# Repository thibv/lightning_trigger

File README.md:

# lightning_trigger
DSLR lightning trigger

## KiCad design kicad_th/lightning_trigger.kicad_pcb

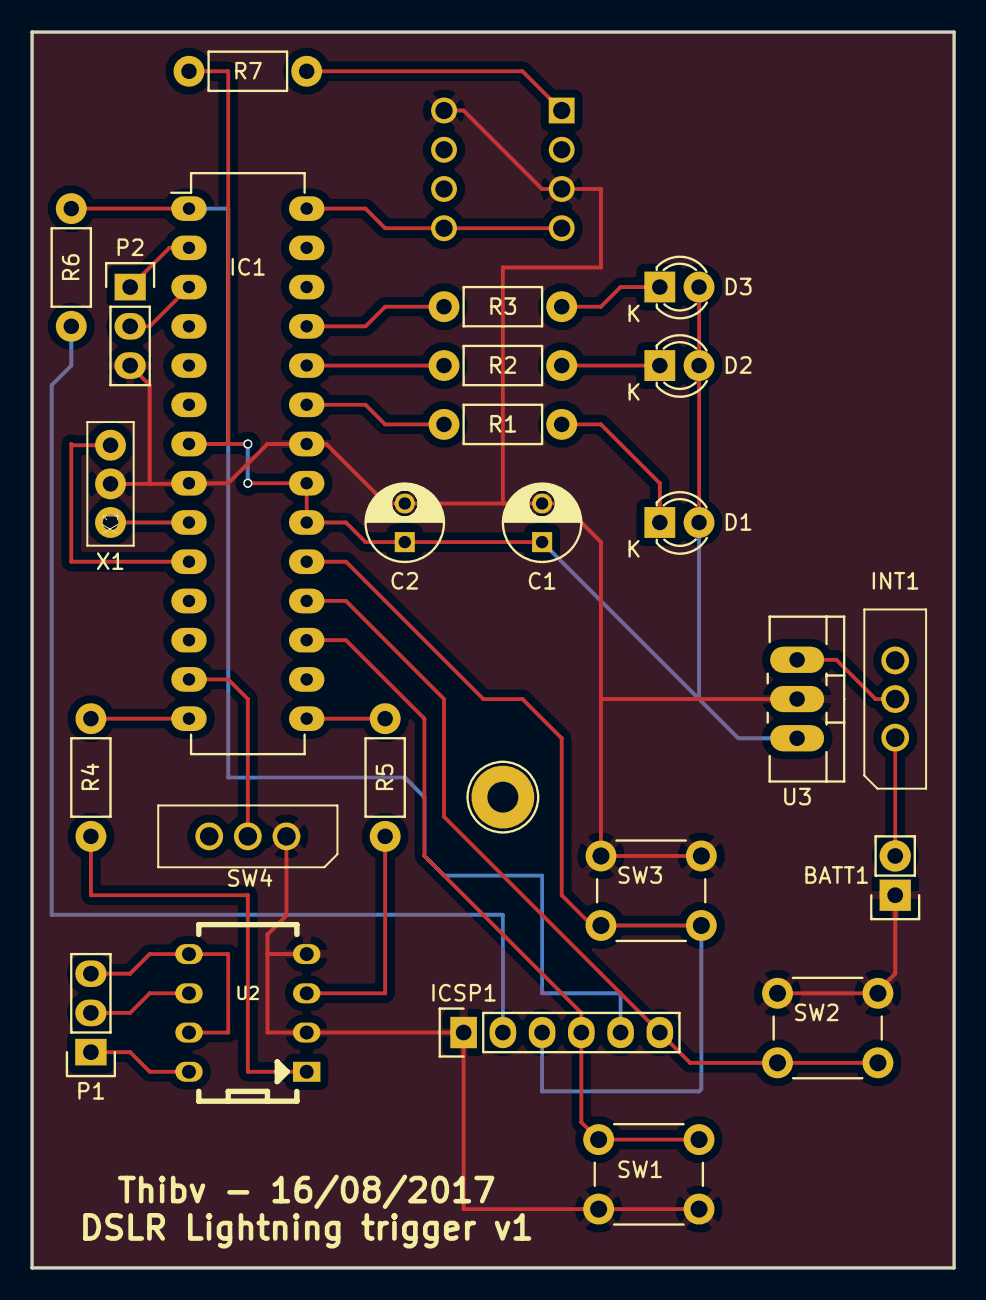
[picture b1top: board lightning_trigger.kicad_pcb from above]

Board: 2 copper layers, 59.7 x 80.0 mm, 26 parts (1 on the bottom side), 29 nets.

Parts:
BATT1: CONN_01X02; Socket_Strip_Straight_1x02
C1: 0.1u; C_Radial_D5_L11_P2.5
C2: 100u; C_Radial_D5_L11_P2.5
D1: LED BLEUE; LED-3MM
D2: LED R-; LED-3MM
D3: LED R+; LED-3MM
IC1: ATMEGA328-P; DIP-28_W7.62mm_LongPads
ICSP1: CONN_02X03; Socket_Strip_Straight_1x06
INT1: DIP-SLIDE-SWITCH(3P-11.6X4.0X5.4+2.0MM); SW3-2.5-11.6X4.0X5.4+2.0MM
P1, P2: CONN_01X03; Socket_Strip_Straight_1x03
R1, R7: 100; Resistor_Horizontal_RM7mm
R2, R3: 330; Resistor_Horizontal_RM7mm
R4, R5: 220; Resistor_Horizontal_RM7mm
R6: 1K; Resistor_Horizontal_RM7mm
SW1, SW2, SW3: SW_PUSH; SW_PUSH_6mm_h13mm
SW4: DIP-SLIDE-SWITCH(3P-11.6X4.0X5.4+2.0MM); SW3-2.5-11.6X4.0X5.4+2.0MM
U1: OPT101P; DIP254P762X419-8
U2: LTV-827; DIP-8
U3: 7805_t; TO-220_Neutral123_Vertical_LargePads
X1: X1; ZTT8.00MT

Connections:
+3V3: ICSP1.2, R6.1
+5V: C1.1, C2.1, D1.2, D2.2, D3.2, IC1.7, IC1.20, IC1.21, R7.2, U3.3
/AF: P1.1, U2.8
/BUTTON_1: IC1.17, ICSP1.4, SW1.2
/BUTTON_2: IC1.18, ICSP1.6, SW2.2
/BUTTON_3: IC1.19, ICSP1.3, SW3.2
/GND_REFLEX: P1.3, U2.5, U2.7
/LED_BLUE: IC1.23, R1.1
/LED_RM: IC1.25, R3.1
/LED_RP: IC1.24, R2.1
/OPTO1: IC1.14, R4.2
/OPTO2: IC1.15, R5.2
/RST: IC1.1, ICSP1.5, R6.2
/RXD: IC1.2, P2.1
/SETTING_1: IC1.13, SW4.2
/SIGNAL: IC1.28, U1.4, U1.5
/TRIGGER: P1.2, U2.6
/TXD: IC1.3, P2.2
/XTAL1: IC1.9, X1.1
/XTAL2: IC1.10, X1.3
GND: BATT1.1, C1.2, C2.2, IC1.8, IC1.22, ICSP1.1, P2.3, SW1.1, SW2.1, SW3.1, SW4.1, U1.3, U1.8, U2.2, U2.4, U3.2, X1.2
unnamed: BATT1.2, INT1.1
unnamed: D1.1, R1.2
unnamed: D2.1, R2.2
unnamed: D3.1, R3.2
unnamed: INT1.2, U3.1
unnamed: R4.1, U2.1
unnamed: R5.1, U2.3
unnamed: R7.1, U1.1

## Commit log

2017-08-16 Add KiCad schematic and PCB for the Through-hole version.
